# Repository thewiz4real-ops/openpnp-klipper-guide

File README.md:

# OpenPnP + Klipper on SKR Mini E3 V3 (Windows + WSL2)

**One repo. Clean steps. Commands clearly marked for Windows or Ubuntu/WSL.**  
This guide fixes common pitfalls and clarifies the *“Z shows −61”* non‑issue (camera focus vs. nozzle Z).

## Quick Start
1. **Bill of Materials:** See [10-bom.md](docs/10-bom.md)
2. **Flash/Host Setup:** See [20-skr-mini-wsl2.md](docs/20-skr-mini-wsl2.md)
3. **Before Starting OpenPnP (each boot):** See [30-before-starting-openpnp.md](docs/30-before-starting-openpnp.md).
4. **OpenPnP ↔ Klipper driver (TCP bridge):** See [40-openpnp-driver.md](docs/40-openpnp-driver.md)
5. **Head rotation via fake extruder (EM/E0):** See [50-rotation-extruder.md](docs/50-rotation-extruder.md)
6. **Lights (ESP32 or SKR fans):** See [60-lights.md](docs/60-lights.md)
7. **Troubleshooting (Step → Problem → Solution):** See [70-troubleshooting.md](docs/70-troubleshooting.md)

👉 Example configs live in [`configs/`](configs/).

## Contributing
Found something to fix? Please open an Issue or a Pull Request.  
See [CONTRIBUTING.md](CONTRIBUTING.md).

## License
- Docs: **CC BY 4.0**
- Code/Configs: **MIT**

*Generated: 2025-08-13 21:21*

---

## Project Notes

- **Attribution:** This machine is **inspired by the LumenPnP open‑source project (v4)**. Most **3D printables** and the **stopper PCB** come from the LumenPnP v4 project.
- **Do not overwrite your own `machine.xml`:** The example in `configs/machine.xml` is **guidance only**. **Do not** replace your working OpenPnP `machine.xml` with it; copy settings over selectively.
- **BOM:** The bill of materials is now in **[10-bom.md](docs/10-bom.md)**.
- **Where to put the ring‑light KiCad project:** place it under **`hardware/ringlight-24v-2x4-osram/`**. (See **hardware/README.md** for folder layout.)

*Notes updated: 2025-08-13 21:35*

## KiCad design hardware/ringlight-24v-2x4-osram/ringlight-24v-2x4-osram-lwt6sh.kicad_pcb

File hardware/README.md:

# Hardware folder

Use this folder to keep mechanical and PCB design files together.

## Subfolders
- `ringlight-24v-2x4-osram/` — **Put your 24 V ring light KiCad project here** (schematic, PCB, 3D, gerbers).
- `z-gantry-juki/` — Models/drawings for the JUKI-compatible Z gantry.

## Mechanical Parts & Printables
- `aluminum-bed` — 460×300 mm bed with 30 mm hole grid and 45 mm camera hole.
- [LumenPnP v4 printables](https://github.com/opulo-inc/lumenpnp) — used for most printed parts in this build.

> Reminder: **Don’t overwrite** your working OpenPnP `machine.xml` with the one in `configs/`. Use that file as **guidance** and copy only the bits you need.

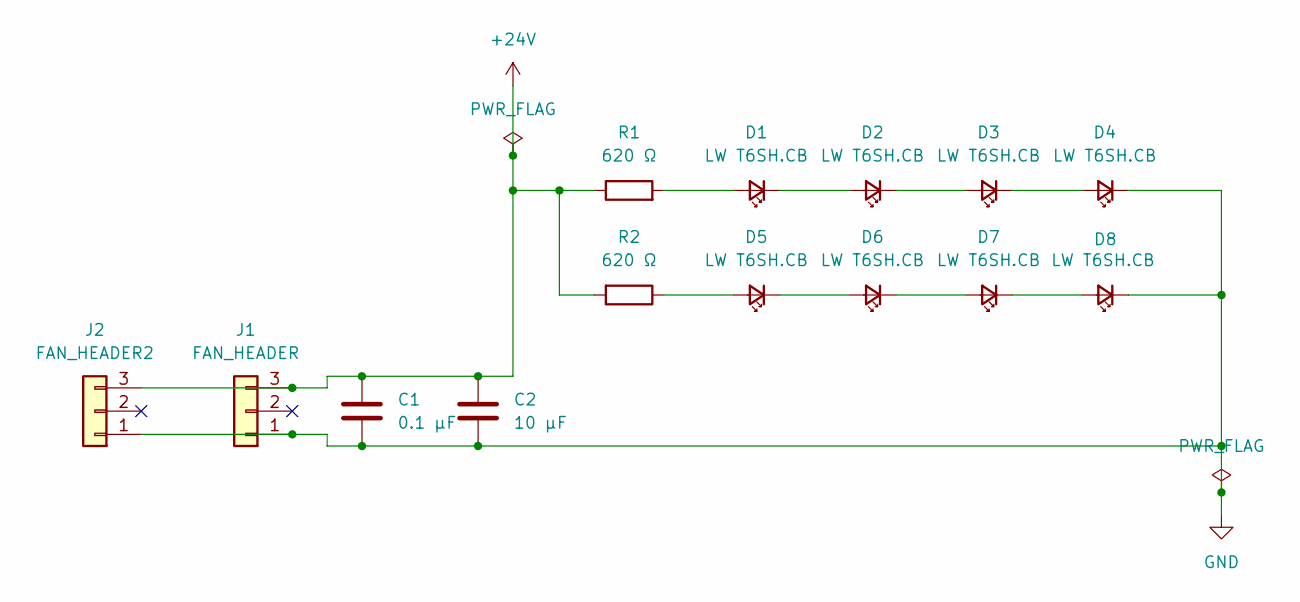
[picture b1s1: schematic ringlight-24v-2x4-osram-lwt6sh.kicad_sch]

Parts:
C1: 0.1 µF; C_0805_2012Metric
C2: 10 µF; C_0805_2012Metric
D1, D2, D3, D4, D5, D6, D7, D8: LW T6SH.CB; LED_PLCC_2835
J1: FAN_HEADER; JST_XH_B3B-XH-A_1x03_P2.50mm_Vertical
J2: FAN_HEADER2; JST_XA_S03B-XASK-1N-BN_1x03_P2.50mm_Horizontal
R1, R2: 620 Ω; R_1210_3225Metric

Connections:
+24V: C1.1, C2.1, J1.3, J2.3, R1.1, R2.2
GND: C1.2, C2.2, D4.1 (K), D8.1 (K), J1.1, J2.1
unnamed: D1.2 (A), R1.2
unnamed: D1.1 (K), D2.2 (A)
unnamed: D2.1 (K), D3.2 (A)
unnamed: D3.1 (K), D4.2 (A)
unnamed: D5.2 (A), R2.1
unnamed: D5.1 (K), D6.2 (A)
unnamed: D6.1 (K), D7.2 (A)
unnamed: D7.1 (K), D8.2 (A)

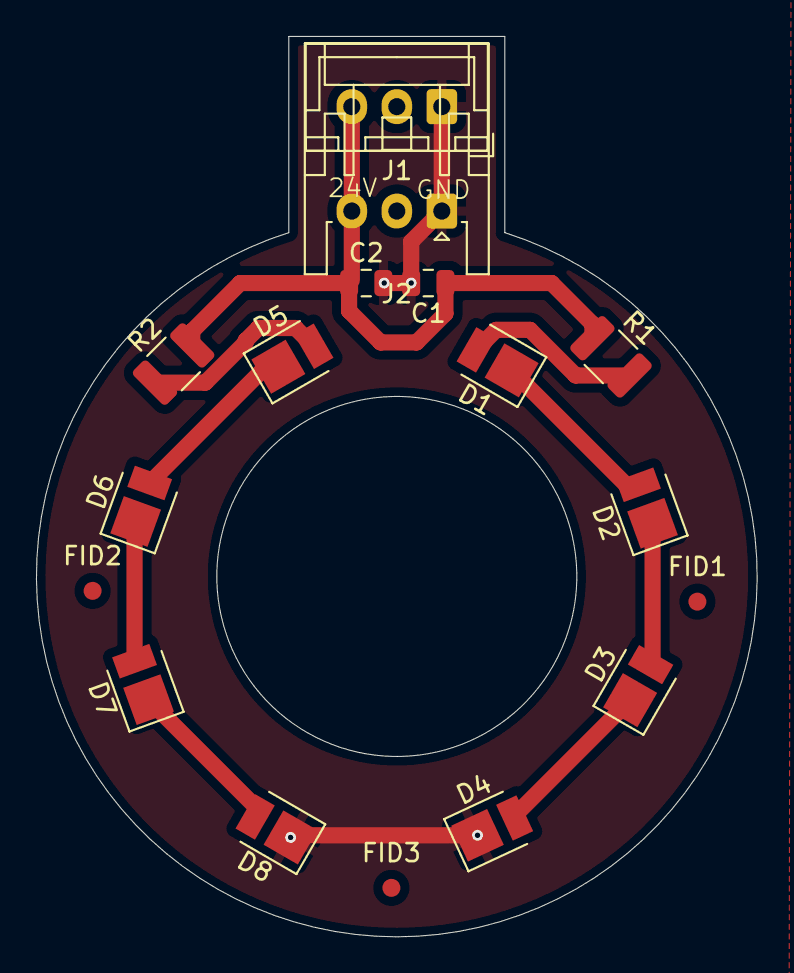
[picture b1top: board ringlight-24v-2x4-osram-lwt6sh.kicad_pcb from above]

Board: 2 copper layers, 40.0 x 50.0 mm, 17 parts (0 on the bottom side), 10 nets.

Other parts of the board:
FID1, FID2, FID3: Fiducial_1mm_Mask2mm

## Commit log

2025-08-13 Initial commit: OpenPnP + Klipper guide, configs, BOM, and templates
    Added full guide for running OpenPnP with Klipper on SKR Mini E3 V3 (Windows/WSL2).
    Includes:
    - Step by step setup docs
    - Config files
    - Troubleshooting
    - Bill of Materials
2025-08-13 Fix README Quick Start links and add BOM at top
2025-08-13 Add per boot startup commands guide before launching OpenPnP
    - Created new docs/25-before-starting-openpnp.md for commands to run each time Windows starts before launching OpenPnP.
    - Moved USB/IP attach and socat bridge instructions out of installation guide.
    - Updated Quick Start in README.md to include the new step after host setup.
2025-08-13 Add per boot startup commands guide before launching OpenPnP
